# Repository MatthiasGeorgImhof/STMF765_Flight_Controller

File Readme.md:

A flight controller inspired by Speedybee F405 v3 but with CAN using F7 MCU. Use flash memory instead of flash card.

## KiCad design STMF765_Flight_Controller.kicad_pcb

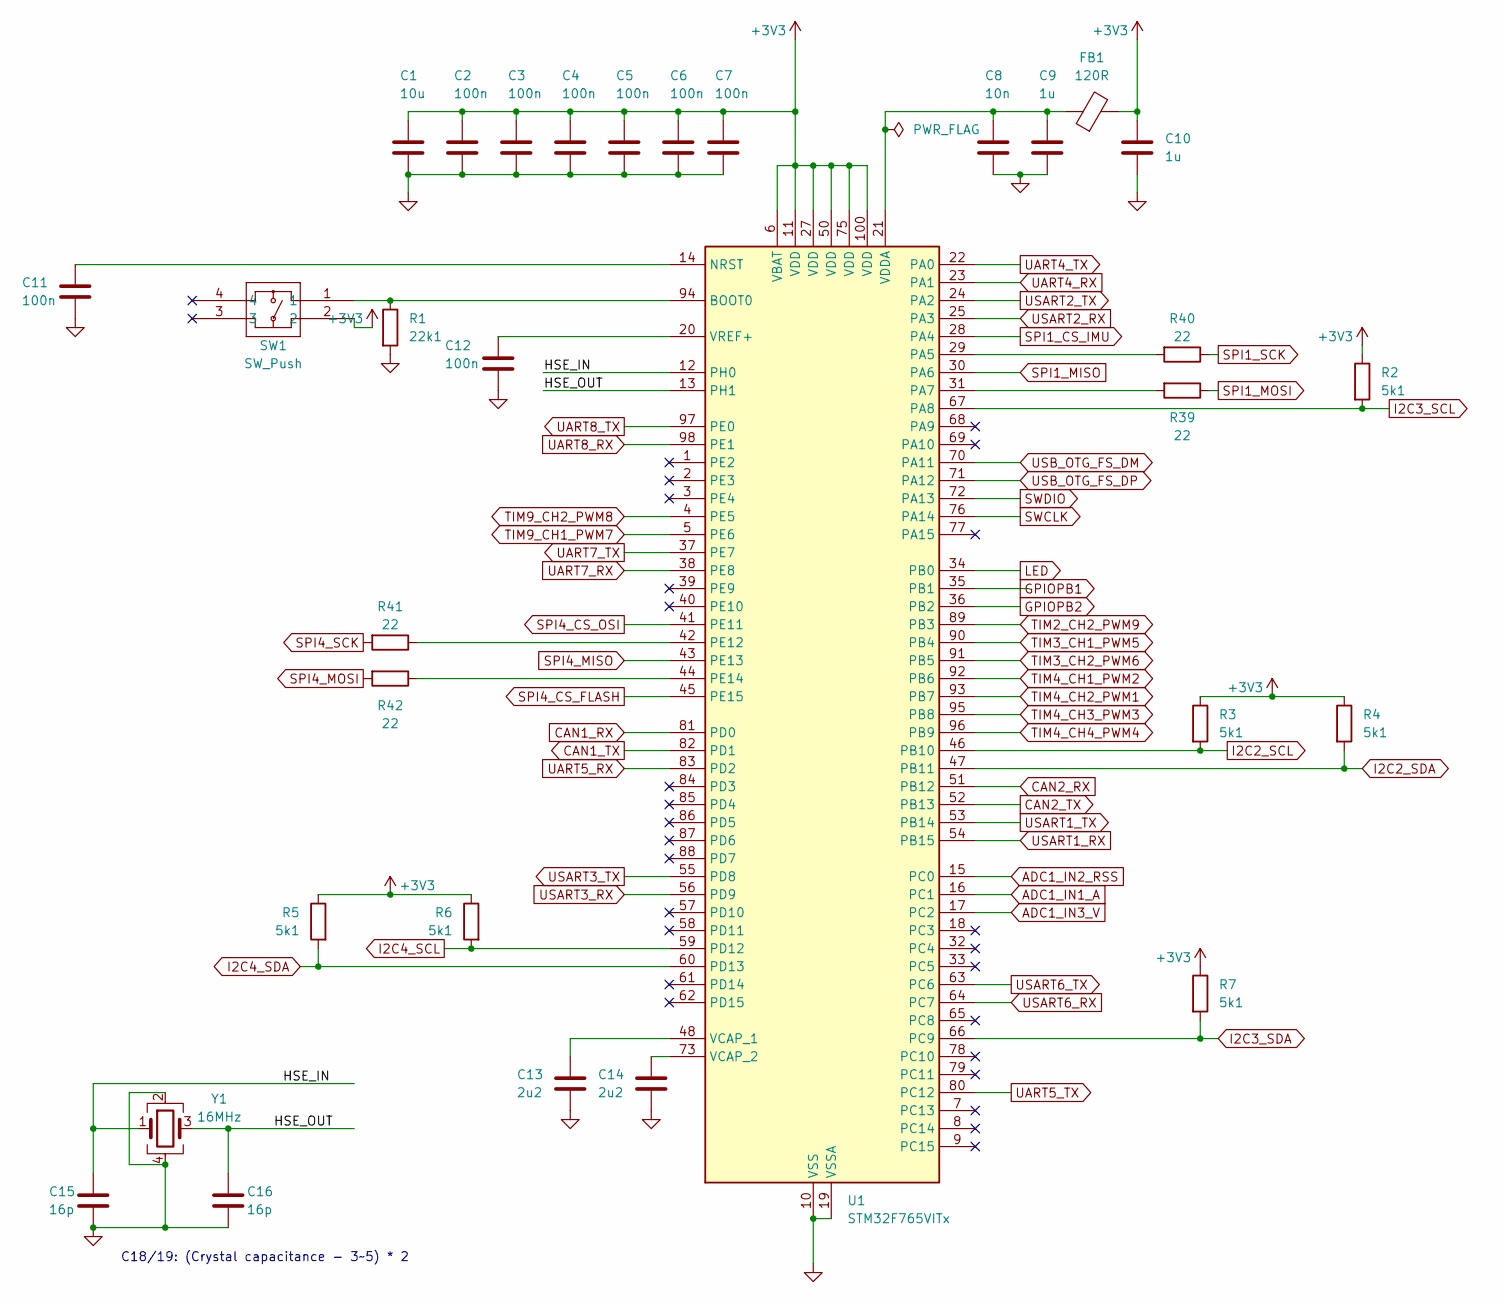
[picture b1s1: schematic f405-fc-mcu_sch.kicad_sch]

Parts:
C1: 10u; C_0603_1608Metric; Voltage 16; Tolerance 10%; Part Number GRT188R61C106KE13D
C2, C3, C4, C5, C6, C7, C11, C12: 100n; C_0201_0603Metric; Voltage 16; Tolerance 10%; Part Number GRM033R61C104KE14D
C8: 10n; C_0201_0603Metric; Voltage 16; Tolerance 10%; Part Number GRM033R61C103KA12D
C9, C10: 1u; C_0201_0603Metric; Voltage 16; Tolerance 10%; Part Number GRM033R61C105ME15D
C13, C14: 2u2; C_0402_1005Metric; Voltage 16; Tolerance 10%; Part Number GRM155R61C225KE44D
C15, C16: 16p; C_0201_0603Metric; Voltage 16; Tolerance 5%; Part Number GRM0335C1H160JA01D
FB1: 120R; L_0603_1608Metric; Part Number MI0603M121R-10
R1: 22k1; R_0201_0603Metric; Tolerance 1%; Part Number RC0201FR-0722K1L
R2, R3, R4, R5, R6, R7: 5k1; R_0201_0603Metric; Tolerance 1%; Part Number RC0402FR-075K1L
R39, R40, R41, R42: 22; R_0201_0603Metric; Tolerance 1%; Part Number RC0402FR-0722RP
SW1: SW_Push; EVPAA602; Part Number EVQPE104K
U1: STM32F765VITx; LQFP-100_14x14mm_P0.5mm; Part Number STM32F765VIT6
Y1: 16MHz; Crystal_SMD_3225-4Pin_3.2x2.5mm; Part Number ECS-80-12-33-JGN-TR

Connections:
+3V3: C1.1, C2.1, C3.1, C4.1, C5.1, C6.1, C7.1, C10.1, FB1.2, R2.1, R3.1, R4.1, R5.1, R6.1, R7.1, SW1.2, U1.6 (VBAT), U1.11 (VDD), U1.27 (VDD), U1.50 (VDD), U1.75 (VDD), U1.100 (VDD); also elsewhere on the board
/MCU/HSE_IN: C15.1, U1.12 (PH0), Y1.1
/MCU/HSE_OUT: C16.1, U1.13 (PH1), Y1.3
ADC1_IN1_A: U1.16 (PC1); also elsewhere on the board
ADC1_IN2_RSS: U1.15 (PC0); also elsewhere on the board
ADC1_IN3_V: U1.17 (PC2); also elsewhere on the board
CAN1_RX: U1.81 (PD0); also elsewhere on the board
CAN1_TX: U1.82 (PD1); also elsewhere on the board
CAN2_RX: U1.51 (PB12); also elsewhere on the board
CAN2_TX: U1.52 (PB13); also elsewhere on the board
GND: C1.2, C2.2, C3.2, C4.2, C5.2, C6.2, C7.2, C8.2, C9.2, C10.2, C11.2, C12.2, C13.2, C14.2, C15.2, C16.2, R1.2, U1.10 (VSS), U1.19 (VSSA), U1.26 (VSS), U1.49 (VSS), U1.74 (VSS), U1.99 (VSS), Y1.2, Y1.4; also elsewhere on the board
GPIOPB1: U1.35 (PB1); also elsewhere on the board
GPIOPB2: U1.36 (PB2); also elsewhere on the board
I2C2_SCL: R3.2, U1.46 (PB10); also elsewhere on the board
I2C2_SDA: R4.2, U1.47 (PB11); also elsewhere on the board
I2C3_SCL: R2.2, U1.67 (PA8); also elsewhere on the board
I2C3_SDA: R7.2, U1.66 (PC9); also elsewhere on the board
I2C4_SCL: R6.2, U1.59 (PD12); also elsewhere on the board
I2C4_SDA: R5.2, U1.60 (PD13); also elsewhere on the board
LED: U1.34 (PB0); also elsewhere on the board
unnamed: R1.1, SW1.1, U1.94 (BOOT0)
unnamed: C11.1, U1.14 (NRST)
unnamed: R40.2, U1.29 (PA5)
unnamed: R39.2, U1.31 (PA7)
unnamed: R41.1, U1.42 (PE12)
unnamed: R42.1, U1.44 (PE14)
unnamed: C13.1, U1.48 (VCAP_1)
unnamed: C14.1, U1.73 (VCAP_2)
unnamed: C8.1, C9.1, FB1.1, U1.21 (VDDA)
unnamed: C12.1, U1.20 (VREF+)
SPI1_CS_IMU: U1.28 (PA4); also elsewhere on the board
SPI1_MISO: U1.30 (PA6); also elsewhere on the board
SPI1_MOSI: R39.1; also elsewhere on the board
SPI1_SCK: R40.1; also elsewhere on the board
SPI4_CS_FLASH: U1.45 (PE15); also elsewhere on the board
SPI4_CS_OSI: U1.41 (PE11); also elsewhere on the board
SPI4_MISO: U1.43 (PE13); also elsewhere on the board
SPI4_MOSI: R42.2; also elsewhere on the board
SPI4_SCK: R41.2; also elsewhere on the board
SWCLK: U1.76 (PA14); also elsewhere on the board
SWDIO: U1.72 (PA13); also elsewhere on the board
TIM2_CH2_PWM9: U1.89 (PB3); also elsewhere on the board
TIM3_CH1_PWM5: U1.90 (PB4); also elsewhere on the board
TIM3_CH2_PWM6: U1.91 (PB5); also elsewhere on the board
TIM4_CH1_PWM2: U1.92 (PB6); also elsewhere on the board
TIM4_CH2_PWM1: U1.93 (PB7); also elsewhere on the board
TIM4_CH3_PWM3: U1.95 (PB8); also elsewhere on the board
TIM4_CH4_PWM4: U1.96 (PB9); also elsewhere on the board
TIM9_CH1_PWM7: U1.5 (PE6); also elsewhere on the board
TIM9_CH2_PWM8: U1.4 (PE5); also elsewhere on the board
UART4_RX: U1.23 (PA1); also elsewhere on the board
UART4_TX: U1.22 (PA0); also elsewhere on the board
UART5_RX: U1.83 (PD2); also elsewhere on the board
UART5_TX: U1.80 (PC12); also elsewhere on the board
UART7_RX: U1.38 (PE8); also elsewhere on the board
UART7_TX: U1.37 (PE7); also elsewhere on the board
UART8_RX: U1.98 (PE1); also elsewhere on the board
UART8_TX: U1.97 (PE0); also elsewhere on the board
USART1_RX: U1.54 (PB15); also elsewhere on the board
USART1_TX: U1.53 (PB14); also elsewhere on the board
USART2_RX: U1.25 (PA3); also elsewhere on the board
USART2_TX: U1.24 (PA2); also elsewhere on the board
USART3_RX: U1.56 (PD9); also elsewhere on the board
USART3_TX: U1.55 (PD8); also elsewhere on the board
USART6_RX: U1.64 (PC7); also elsewhere on the board
USART6_TX: U1.63 (PC6); also elsewhere on the board
USB_OTG_FS_DM: U1.70 (PA11); also elsewhere on the board
USB_OTG_FS_DP: U1.71 (PA12); also elsewhere on the board

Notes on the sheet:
C18/19: (Crystal capacitance - 3~5) * 2

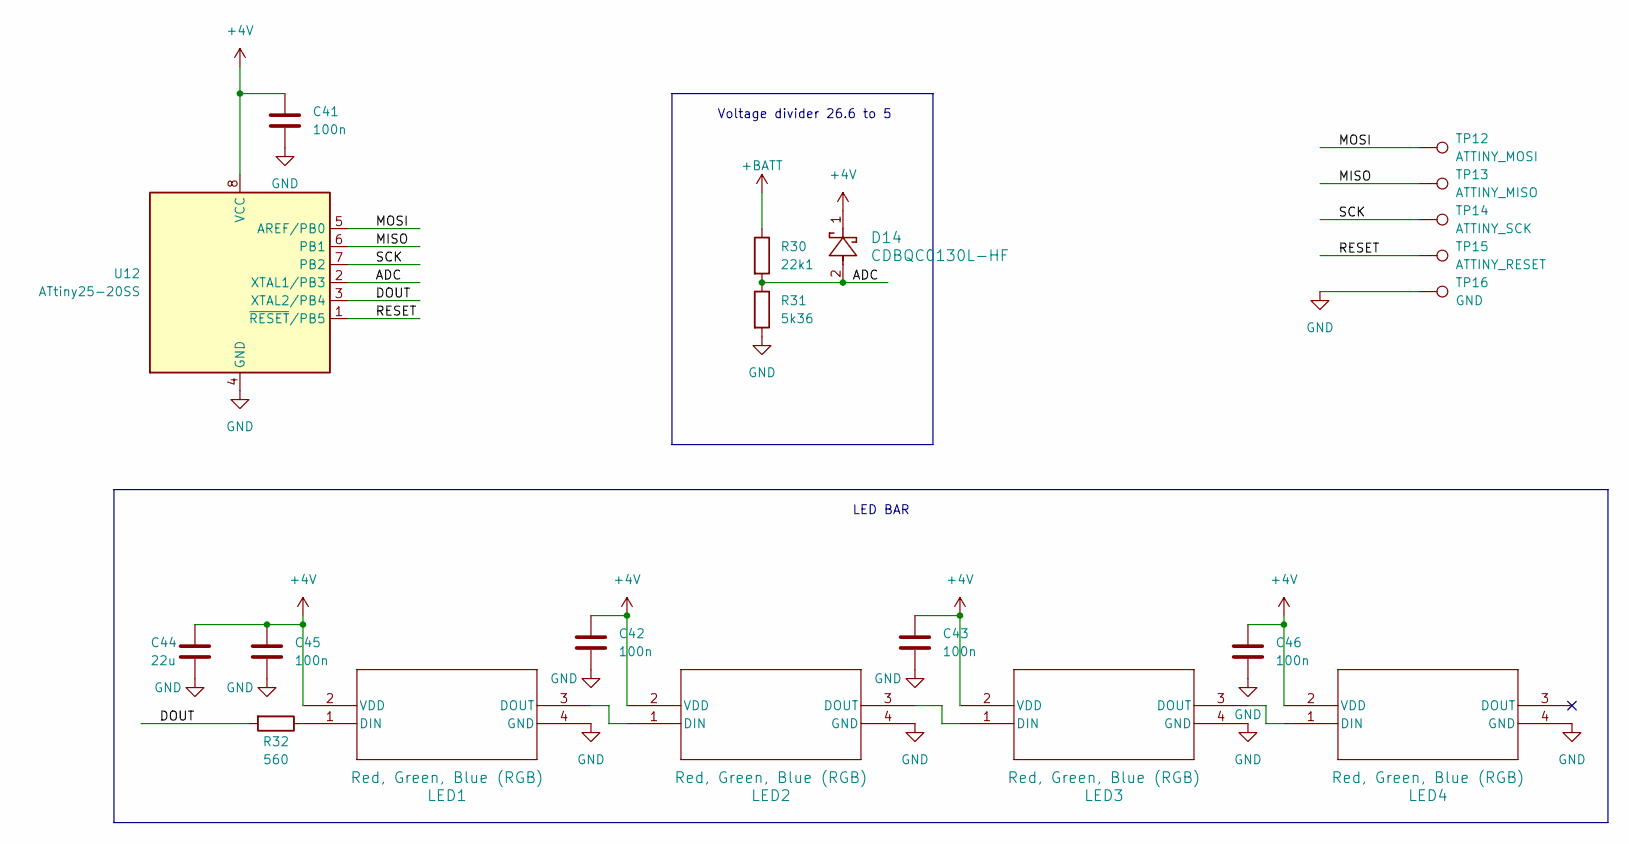
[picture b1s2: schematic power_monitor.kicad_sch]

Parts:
C41, C43, C45, C46: 100n; C_0201_0603Metric; Voltage 16; Tolerance 10%; Part Number GRM033R61C104KE14D
C42: 100n; C_0201_0603Metric; Tolerance 10%; Voltage 16; Part Number GRM033R61C104KE14D
C44: 22u; C_1206_3216Metric; Tolerance 10%; Voltage 16; Part Number GRT31CC81C226KE01L
D14: CDBQC0130L-HF; SDO_0201-DFN0603_CIP; Part Number CDBQC0130L-HF
LED1, LED2, LED3, LED4: Red, Green, Blue (RGB); IN-PI15_INL; Part Number IN-PI15TAT5R5G5B
R30: 22k1; R_0201_0603Metric; Tolerance 1%; Part Number RC0201FR-0720K5L
R31: 5k36; R_0201_0603Metric; Tolerance 1%; Part Number RC0201FR-074K99L
R32: 560; R_0201_0603Metric; Tolerance 1%; Part Number RC0402FR-07560RL
TP12: ATTINY_MOSI; TestPoint_Pad_1.0x1.5mm
TP13: ATTINY_MISO; TestPoint_Pad_1.0x1.5mm
TP14: ATTINY_SCK; TestPoint_Pad_1.0x1.5mm
TP15: ATTINY_RESET; TestPoint_Pad_1.0x1.5mm
TP16: GND; TestPoint_Pad_1.0x1.5mm
U12: ATtiny25-20SS; SOIC-8_3.9x4.9mm_P1.27mm; Part Number ATTINY25-20SSU

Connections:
+4V: C41.1, C42.1, C43.1, C44.1, C45.1, C46.1, D14.1, LED1.2 (VDD), LED2.2 (VDD), LED3.2 (VDD), LED4.2 (VDD), U12.8 (VCC); also elsewhere on the board
+BATT: R30.1; also elsewhere on the board
/Power Monitor/ADC: D14.2, R30.2, R31.1, U12.2 (XTAL1/PB3)
/Power Monitor/DOUT: R32.2, U12.3 (XTAL2/PB4)
/Power Monitor/MISO: TP13.1, U12.6 (PB1)
/Power Monitor/MOSI: TP12.1, U12.5 (AREF/PB0)
/Power Monitor/RESET: TP15.1, U12.1 (~RESET/PB5)
/Power Monitor/SCK: TP14.1, U12.7 (PB2)
GND: C41.2, C42.2, C43.2, C44.2, C45.2, C46.2, LED1.4 (GND), LED2.4 (GND), LED3.4 (GND), LED4.4 (GND), R31.2, TP16.1, U12.4 (GND); also elsewhere on the board
unnamed: LED1.1 (DIN), R32.1
unnamed: LED1.3 (DOUT), LED2.1 (DIN)
unnamed: LED2.3 (DOUT), LED3.1 (DIN)
unnamed: LED3.3 (DOUT), LED4.1 (DIN)

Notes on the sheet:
Voltage divider 26.6 to 5
LED BAR

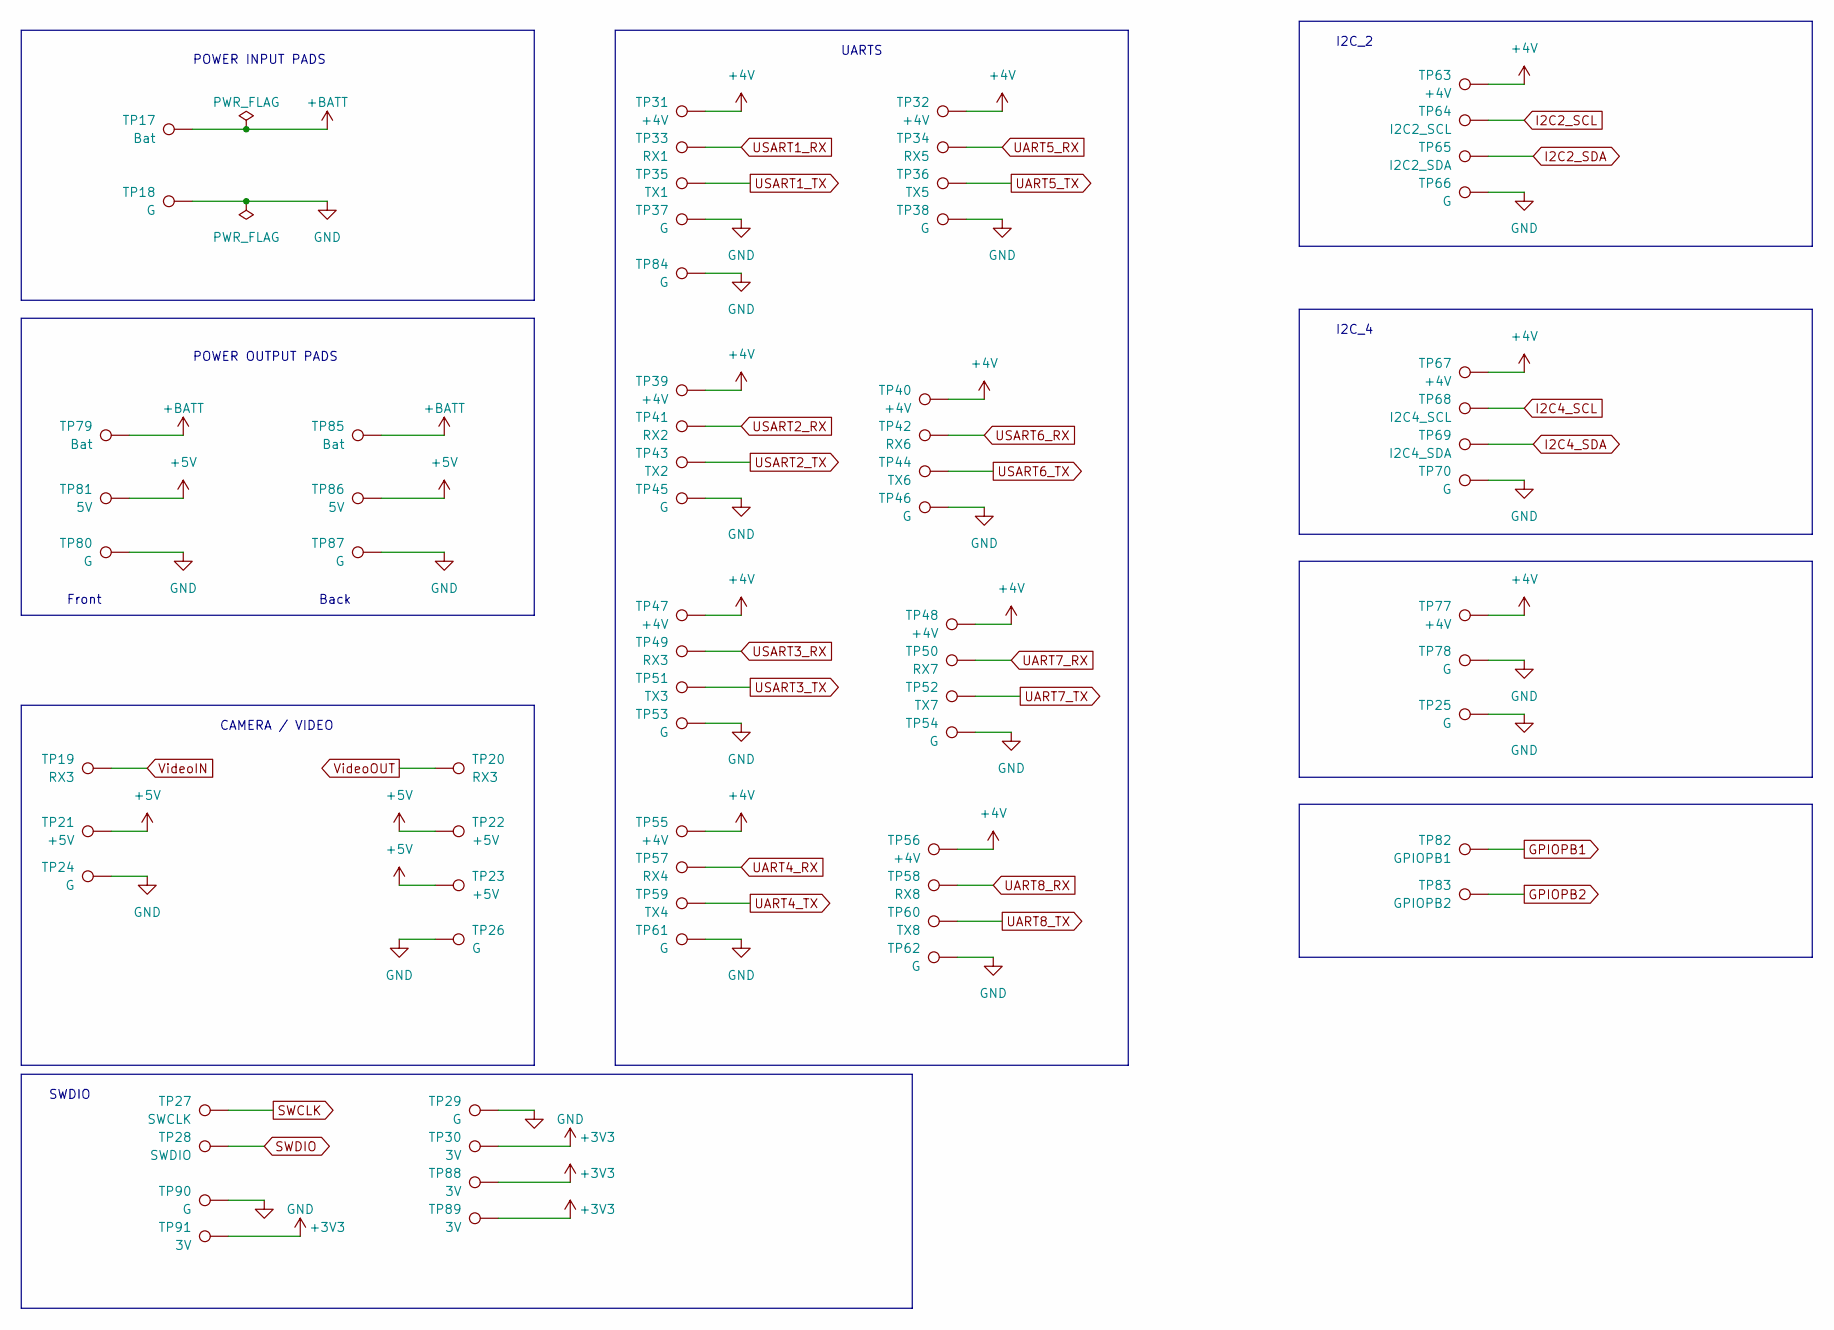
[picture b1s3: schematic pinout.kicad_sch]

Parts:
TP17: Bat; TestPoint_Pad_1.5x1.5mm
TP18: G; TestPoint_Pad_1.5x1.5mm
TP19, TP20, TP49: RX3; TestPoint_Pad_1.0x1.5mm
TP21, TP22, TP23: +5V; TestPoint_Pad_1.0x1.5mm
TP24, TP25, TP26, TP29, TP37, TP38, TP45, TP46, TP53, TP54, TP61, TP62, TP66, TP70, TP78, TP80, TP84, TP87, TP90: G; TestPoint_Pad_1.0x1.5mm
TP27: SWCLK; TestPoint_Pad_1.0x1.5mm
TP28: SWDIO; TestPoint_Pad_1.0x1.5mm
TP30, TP88, TP89, TP91: 3V; TestPoint_Pad_1.0x1.5mm
TP31, TP32, TP39, TP40, TP47, TP48, TP55, TP56, TP63, TP67, TP77: +4V; TestPoint_Pad_1.0x1.5mm
TP33: RX1; TestPoint_Pad_1.0x1.5mm
TP34: RX5; TestPoint_Pad_1.0x1.5mm
TP35: TX1; TestPoint_Pad_1.0x1.5mm
TP36: TX5; TestPoint_Pad_1.0x1.5mm
TP41: RX2; TestPoint_Pad_1.0x1.5mm
TP42: RX6; TestPoint_Pad_1.0x1.5mm
TP43: TX2; TestPoint_Pad_1.0x1.5mm
TP44: TX6; TestPoint_Pad_1.0x1.5mm
TP50: RX7; TestPoint_Pad_1.0x1.5mm
TP51: TX3; TestPoint_Pad_1.0x1.5mm
TP52: TX7; TestPoint_Pad_1.0x1.5mm
TP57: RX4; TestPoint_Pad_1.0x1.5mm
TP58: RX8; TestPoint_Pad_1.0x1.5mm
TP59: TX4; TestPoint_Pad_1.0x1.5mm
TP60: TX8; TestPoint_Pad_1.0x1.5mm
TP64: I2C2_SCL; TestPoint_Pad_1.0x1.5mm
TP65: I2C2_SDA; TestPoint_Pad_1.0x1.5mm
TP68: I2C4_SCL; TestPoint_Pad_1.0x1.5mm
TP69: I2C4_SDA; TestPoint_Pad_1.0x1.5mm
TP79, TP85: Bat; TestPoint_Pad_1.0x1.5mm
TP81, TP86: 5V; TestPoint_Pad_1.0x1.5mm
TP82: GPIOPB1; TestPoint_Pad_1.0x1.5mm
TP83: GPIOPB2; TestPoint_Pad_1.0x1.5mm

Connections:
+3V3: TP30.1, TP88.1, TP89.1, TP91.1; also elsewhere on the board
+4V: TP31.1, TP32.1, TP39.1, TP40.1, TP47.1, TP48.1, TP55.1, TP56.1, TP63.1, TP67.1, TP77.1; also elsewhere on the board
+5V: TP21.1, TP22.1, TP23.1, TP81.1, TP86.1; also elsewhere on the board
+BATT: TP17.1, TP79.1, TP85.1; also elsewhere on the board
GND: TP18.1, TP24.1, TP25.1, TP26.1, TP29.1, TP37.1, TP38.1, TP45.1, TP46.1, TP53.1, TP54.1, TP61.1, TP62.1, TP66.1, TP70.1, TP78.1, TP80.1, TP84.1, TP87.1, TP90.1; also elsewhere on the board
GPIOPB1: TP82.1; also elsewhere on the board
GPIOPB2: TP83.1; also elsewhere on the board
I2C2_SCL: TP64.1; also elsewhere on the board
I2C2_SDA: TP65.1; also elsewhere on the board
I2C4_SCL: TP68.1; also elsewhere on the board
I2C4_SDA: TP69.1; also elsewhere on the board
SWCLK: TP27.1; also elsewhere on the board
SWDIO: TP28.1; also elsewhere on the board
UART4_RX: TP57.1; also elsewhere on the board
UART4_TX: TP59.1; also elsewhere on the board
UART5_RX: TP34.1; also elsewhere on the board
UART5_TX: TP36.1; also elsewhere on the board
UART7_RX: TP50.1; also elsewhere on the board
UART7_TX: TP52.1; also elsewhere on the board
UART8_RX: TP58.1; also elsewhere on the board
UART8_TX: TP60.1; also elsewhere on the board
USART1_RX: TP33.1; also elsewhere on the board
USART1_TX: TP35.1; also elsewhere on the board
USART2_RX: TP41.1; also elsewhere on the board
USART2_TX: TP43.1; also elsewhere on the board
USART3_RX: TP49.1; also elsewhere on the board
USART3_TX: TP51.1; also elsewhere on the board
USART6_RX: TP42.1; also elsewhere on the board
USART6_TX: TP44.1; also elsewhere on the board
VideoIN: TP19.1; also elsewhere on the board
VideoOUT: TP20.1; also elsewhere on the board

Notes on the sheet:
Back
Front
I2C_2
I2C_4
UARTS
CAMERA / VIDEO
POWER OUTPUT PADS
POWER INPUT PADS
SWDIO

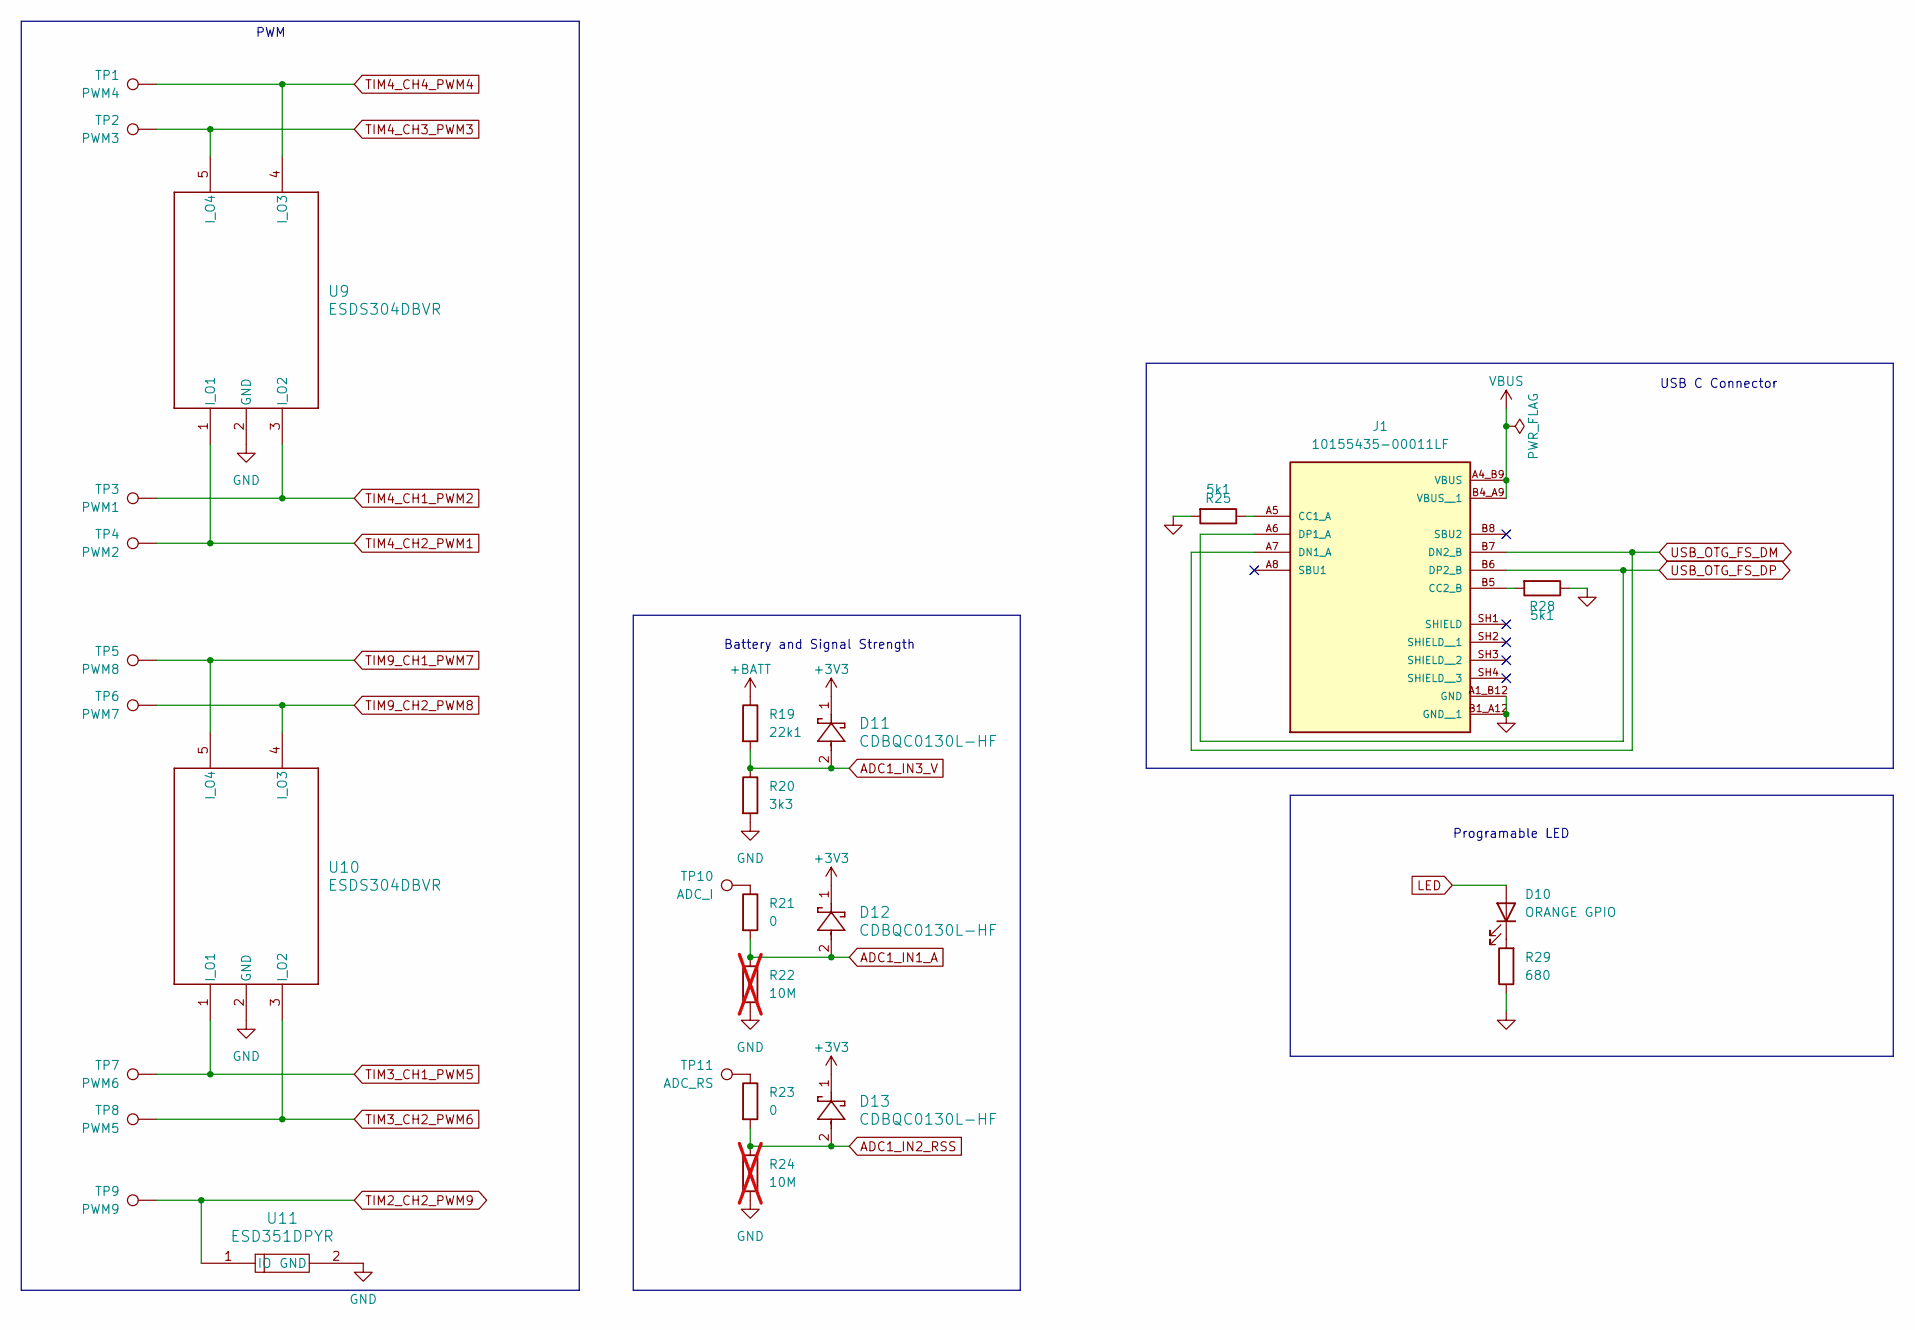
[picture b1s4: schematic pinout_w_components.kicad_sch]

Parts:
D10: ORANGE GPIO; LED_0402_1005Metric; Part Number VLMY1500-GS08
D11, D12, D13: CDBQC0130L-HF; SDO_0201-DFN0603_CIP; Part Number CDBQC0130L-HF
J1: 10155435-00011LF; AMPHENOL_10155435-00011LF; Part Number 10155435-00011LF
R19: 22k1; R_0201_0603Metric; Tolerance 1%; Part Number RC0201FR-0722K1L
R20: 3k3; R_0201_0603Metric; Tolerance 1%; Part Number RC0201FR-073K3L
R21, R23: 0; R_0201_0603Metric; Tolerance 1%; Part Number RC0402FR-070RL
R22: 10M; R_0201_0603Metric; Tolerance 1%; Part Number RC0201JR-0710ML; not fitted
R24: 10M; R_0201_0603Metric; Tolerance 5%; Part Number RC0201JR-0710ML; not fitted
R25, R28: 5k1; R_0201_0603Metric; Tolerance 1%; Part Number RC0402FR-075K1L
R29: 680; R_0201_0603Metric; Tolerance 1%; Part Number RC0402FR-07680RL
TP1: PWM4; TestPoint_Pad_1.0x1.5mm
TP2: PWM3; TestPoint_Pad_1.0x1.5mm
TP3: PWM1; TestPoint_Pad_1.0x1.5mm
TP4: PWM2; TestPoint_Pad_1.0x1.5mm
TP5: PWM8; TestPoint_Pad_1.0x1.5mm
TP6: PWM7; TestPoint_Pad_1.0x1.5mm
TP7: PWM6; TestPoint_Pad_1.0x1.5mm
TP8: PWM5; TestPoint_Pad_1.0x1.5mm
TP9: PWM9; TestPoint_Pad_1.0x1.5mm
TP10: ADC_I; TestPoint_Pad_1.0x1.5mm
TP11: ADC_RS; TestPoint_Pad_1.0x1.5mm
U9, U10: ESDS304DBVR; DBV0005A_L; Part Number ESDS304DBVR
U11: ESD351DPYR; DPY2_TEX; Part Number ESD351DPYR

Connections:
+3V3: D11.1, D12.1, D13.1; also elsewhere on the board
+BATT: R19.1; also elsewhere on the board
ADC1_IN1_A: D12.2, R21.2, R22.1; also elsewhere on the board
ADC1_IN2_RSS: D13.2, R23.2, R24.1; also elsewhere on the board
ADC1_IN3_V: D11.2, R19.2, R20.1; also elsewhere on the board
GND: J1.A1_B12 (GND), J1.B1_A12 (GND__1), R20.2, R22.2, R24.2, R25.2, R28.1, R29.1, U9.2 (GND), U10.2 (GND), U11.2 (GND); also elsewhere on the board
LED: D10.2 (A); also elsewhere on the board
unnamed: D10.1 (K), R29.2
unnamed: J1.A5 (CC1_A), R25.1
unnamed: J1.B5 (CC2_B), R28.2
unnamed: R21.1, TP10.1
unnamed: R23.1, TP11.1
TIM2_CH2_PWM9: TP9.1, U11.1 (IO); also elsewhere on the board
TIM3_CH1_PWM5: TP7.1, U10.1 (I_O1); also elsewhere on the board
TIM3_CH2_PWM6: TP8.1, U10.3 (I_O2); also elsewhere on the board
TIM4_CH1_PWM2: TP3.1, U9.3 (I_O2); also elsewhere on the board
TIM4_CH2_PWM1: TP4.1, U9.1 (I_O1); also elsewhere on the board
TIM4_CH3_PWM3: TP2.1, U9.5 (I_O4); also elsewhere on the board
TIM4_CH4_PWM4: TP1.1, U9.4 (I_O3); also elsewhere on the board
TIM9_CH1_PWM7: TP5.1, U10.5 (I_O4); also elsewhere on the board
TIM9_CH2_PWM8: TP6.1, U10.4 (I_O3); also elsewhere on the board
USB_OTG_FS_DM: J1.A7 (DN1_A), J1.B7 (DN2_B); also elsewhere on the board
USB_OTG_FS_DP: J1.A6 (DP1_A), J1.B6 (DP2_B); also elsewhere on the board
VBUS: J1.A4_B9 (VBUS), J1.B4_A9 (VBUS__1); also elsewhere on the board

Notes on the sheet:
Battery and Signal Strength
Programable LED
PWM
USB C Connector

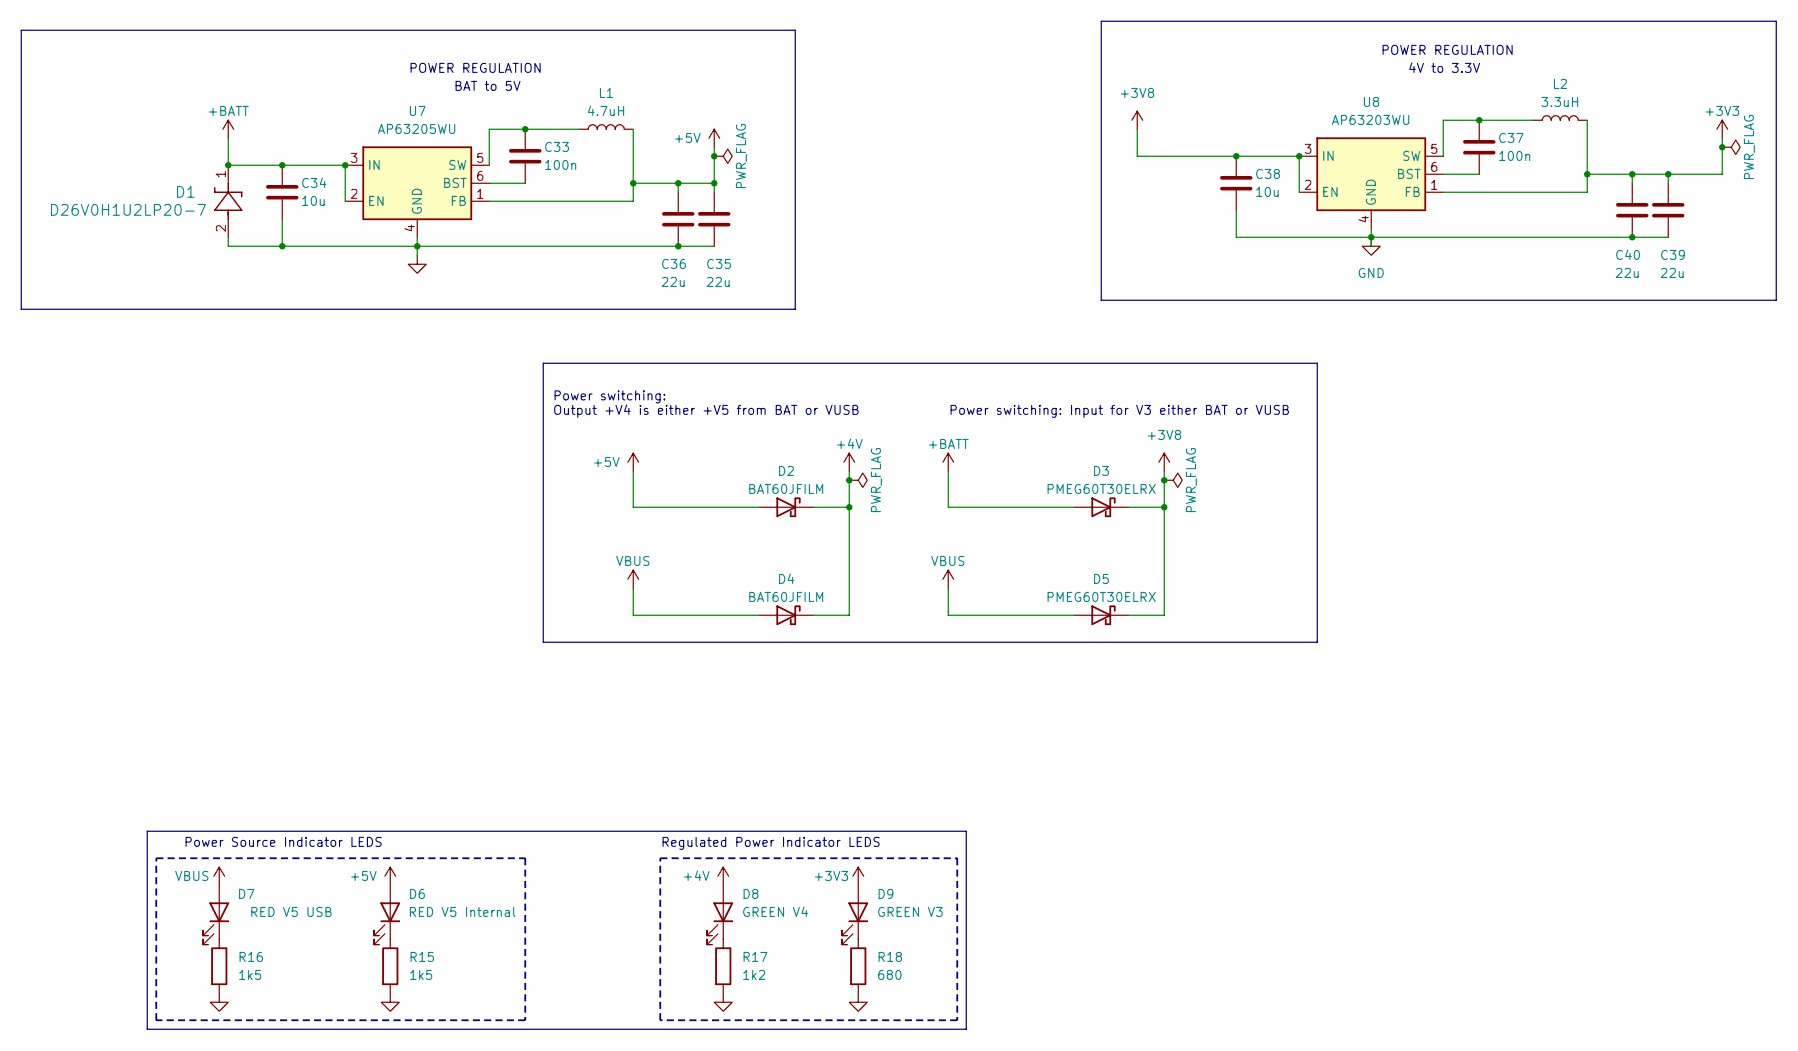
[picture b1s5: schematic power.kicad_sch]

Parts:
C33, C37: 100n; C_0201_0603Metric; Voltage 16; Tolerance 10%; Part Number GRM033R61C104KE14D
C34, C38: 10u; C_1206_3216Metric; Voltage 50; Tolerance 10%; Part Number GRT31CR61H106KE01L
C35, C36, C39, C40: 22u; C_1206_3216Metric; Voltage 16; Tolerance 10%; Part Number GRT31CC81C226KE01L
D1: D26V0H1U2LP20-7; U-DFN2020-2_DIO-L; Voltage 40; Part Number D26V0H1U2LP20-7
D2, D4: BAT60JFILM; D_SOD-323; Voltage 10; Part Number BAT60JFILM
D3, D5: PMEG60T30ELRX; Nexperia_CFP3_SOD-123W; Voltage 60; Part Number PMEG60T30ELRX
D6: RED V5 Internal; LED_0402_1005Metric; Part Number VLMS1500-GS08
D7: RED V5 USB; LED_0402_1005Metric; Part Number VLMS1500-GS08
D8: GREEN V4; LED_0402_1005Metric; Part Number VLMG1500-GS08
D9: GREEN V3; LED_0402_1005Metric; Part Number VLMG1500-GS08
L1: 4.7uH; IND_DFE322520FD-4R7M=P2_MUR; Part Number DFE322520FD-4R7M=P2
L2: 3.3uH; IND_DFE322520FD-4R7M=P2_MUR; Part Number DFE322512F-3R3M=P2
R15, R16: 1k5; R_0201_0603Metric; Tolerance 1%; Part Number RC0402FR-071K5L
R17: 1k2; R_0201_0603Metric; Tolerance 1%; Part Number RC0402FR-071K5L
R18: 680; R_0201_0603Metric; Tolerance 1%; Part Number RC0402FR-07680RL
U7: AP63205WU; TSOT-23-6; Part Number AP63205WU-7
U8: AP63203WU; TSOT-23-6; Part Number AP63203WU-7

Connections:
+3V3: C39.1, C40.1, D9.2 (A), L2.2, U8.1 (FB); also elsewhere on the board
+3V8: C38.1, D3.1 (K), D5.1 (K), U8.2 (EN), U8.3 (IN)
+4V: D2.1 (K), D4.1 (K), D8.2 (A); also elsewhere on the board
+5V: C35.1, C36.1, D2.2 (A), D6.2 (A), L1.2, U7.1 (FB); also elsewhere on the board
+BATT: C34.1, D1.1, D3.2 (A), U7.2 (EN), U7.3 (IN); also elsewhere on the board
GND: C34.2, C35.2, C36.2, C38.2, C39.2, C40.2, D1.2, R15.2, R16.2, R17.2, R18.2, U7.4 (GND), U8.4 (GND); also elsewhere on the board
unnamed: D6.1 (K), R15.1
unnamed: D7.1 (K), R16.1
unnamed: D8.1 (K), R17.1
unnamed: D9.1 (K), R18.1
unnamed: C33.2, U7.6 (BST)
unnamed: C33.1, L1.1, U7.5 (SW)
unnamed: C37.2, U8.6 (BST)
unnamed: C37.1, L2.1, U8.5 (SW)
VBUS: D4.2 (A), D5.2 (A), D7.2 (A); also elsewhere on the board

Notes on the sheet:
Power switching: Output +V4 is either +V5 from BAT or VUSB
BAT to 5V
Power switching: Input for V3 either BAT or VUSB
POWER REGULATION
Power Source Indicator LEDS
4V to 3.3V
Regulated Power Indicator LEDS

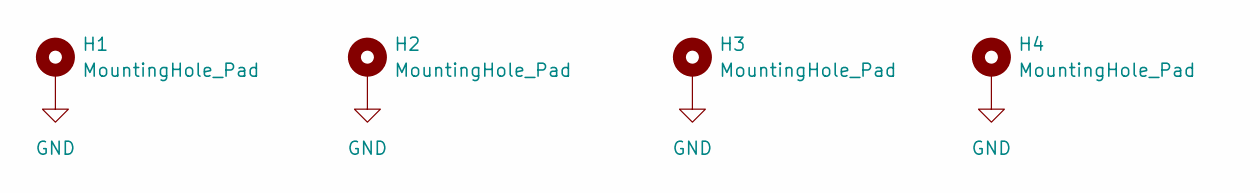
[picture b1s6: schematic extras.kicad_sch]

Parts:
H1, H2, H3, H4: MountingHole_Pad; MountingHole_4.3mm_M4_Pad_Via_Custom

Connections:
GND: H1.1, H2.1, H3.1, H4.1; also elsewhere on the board
